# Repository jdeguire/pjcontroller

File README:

I need to put something here, I guess...

If you plan on building the firmware, you'll need a few things.
--avr-gcc (Ubuntu's repo has this as 'gcc-avr' for some reason)
--avr-binutils
--avr-libc
--avrdude
--scons, which in turn requires Python

The SConscript/SConstruct files assume that you are using the avr-gcc toolchain and avrdude as your ICSP programmer.  You can modify the files if this is not the case.

Schematics are created with KiCAD.

Stuff in hardware/spice was made using LTSpiceIV.  This runs fine under WINE.

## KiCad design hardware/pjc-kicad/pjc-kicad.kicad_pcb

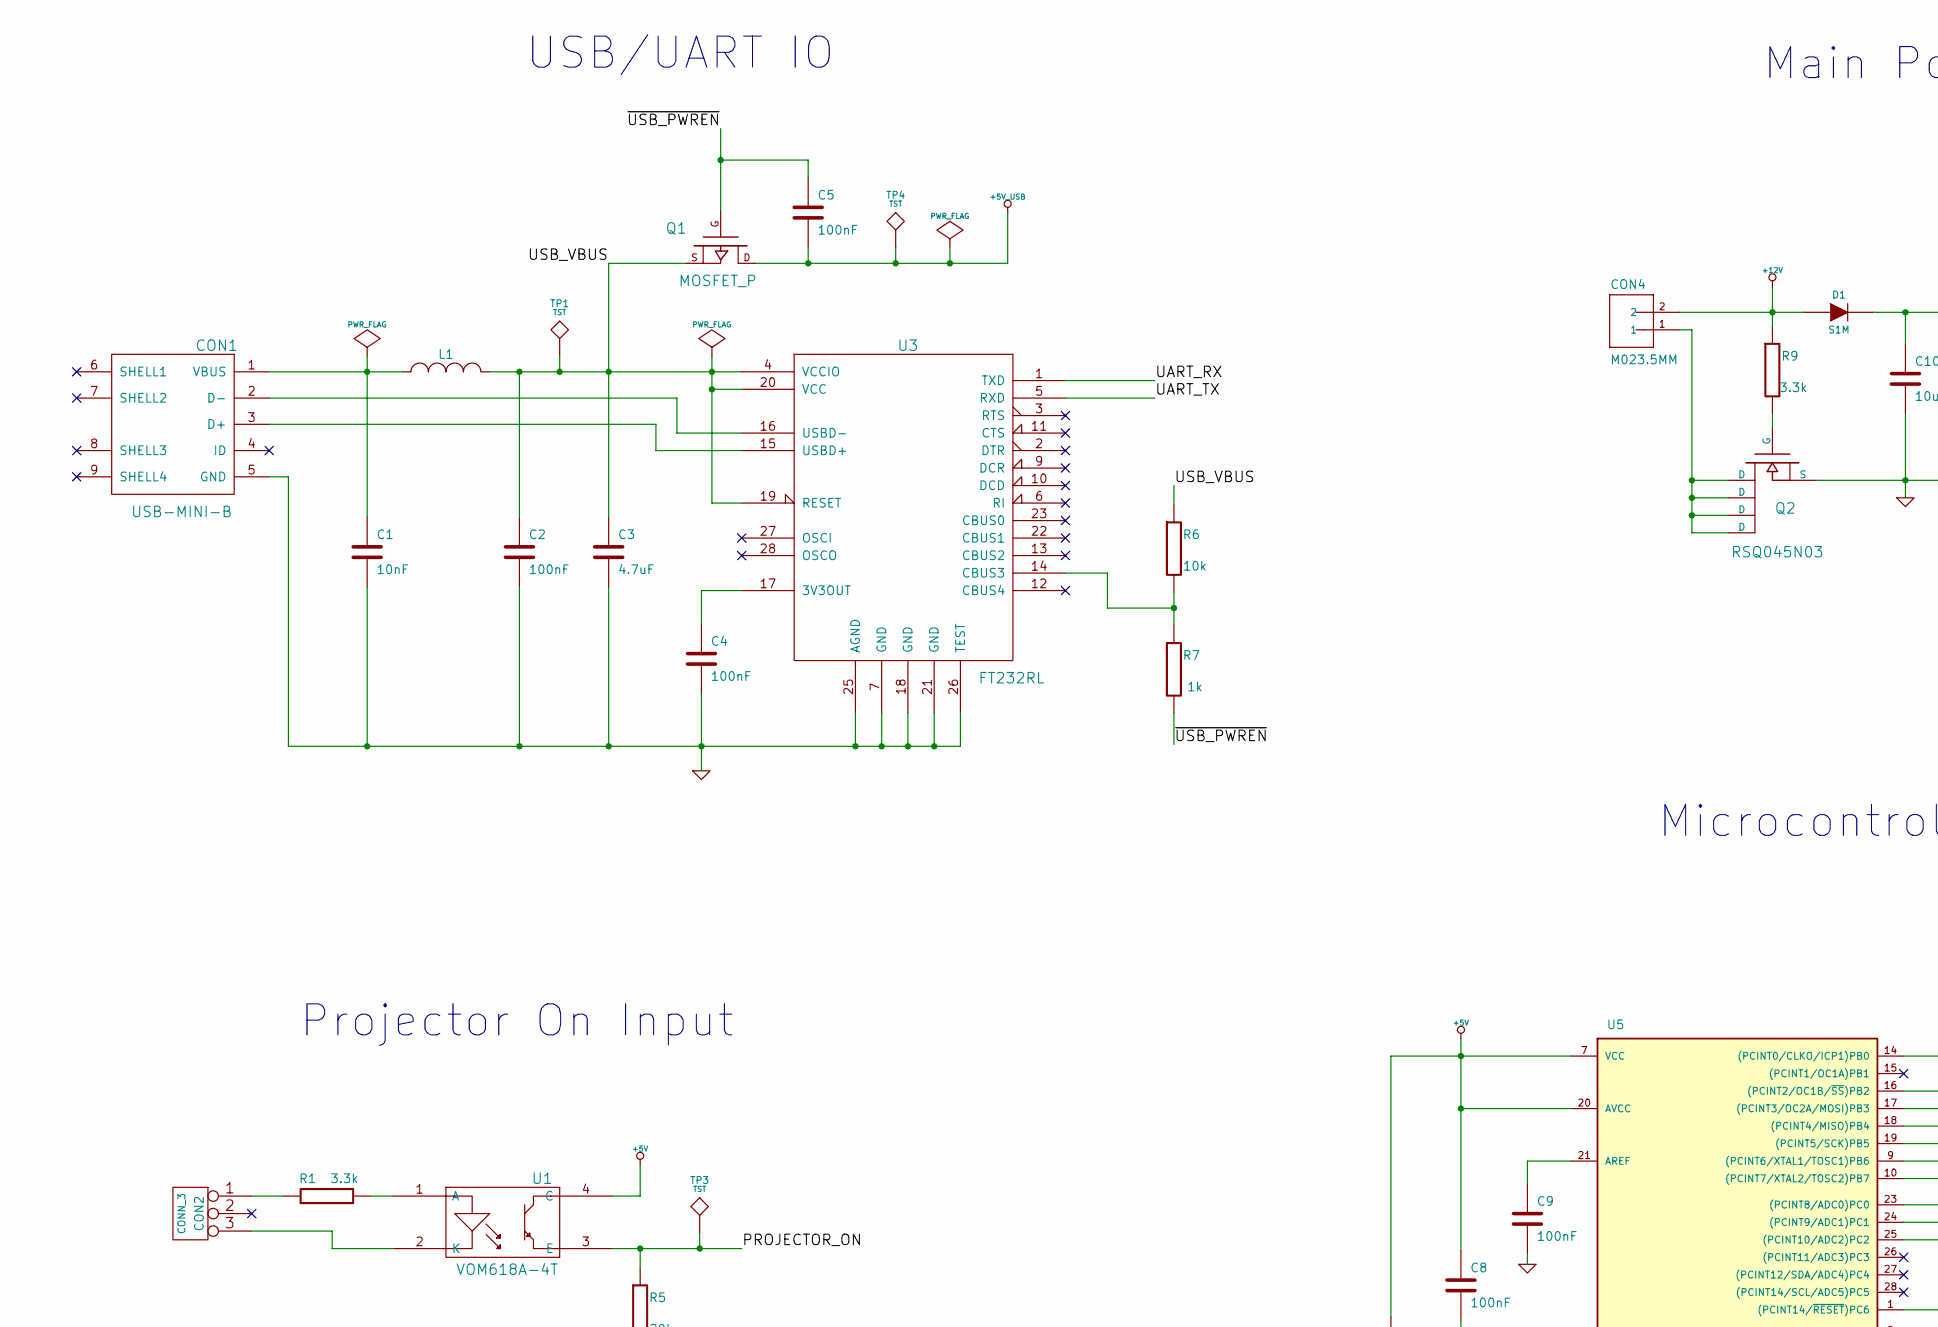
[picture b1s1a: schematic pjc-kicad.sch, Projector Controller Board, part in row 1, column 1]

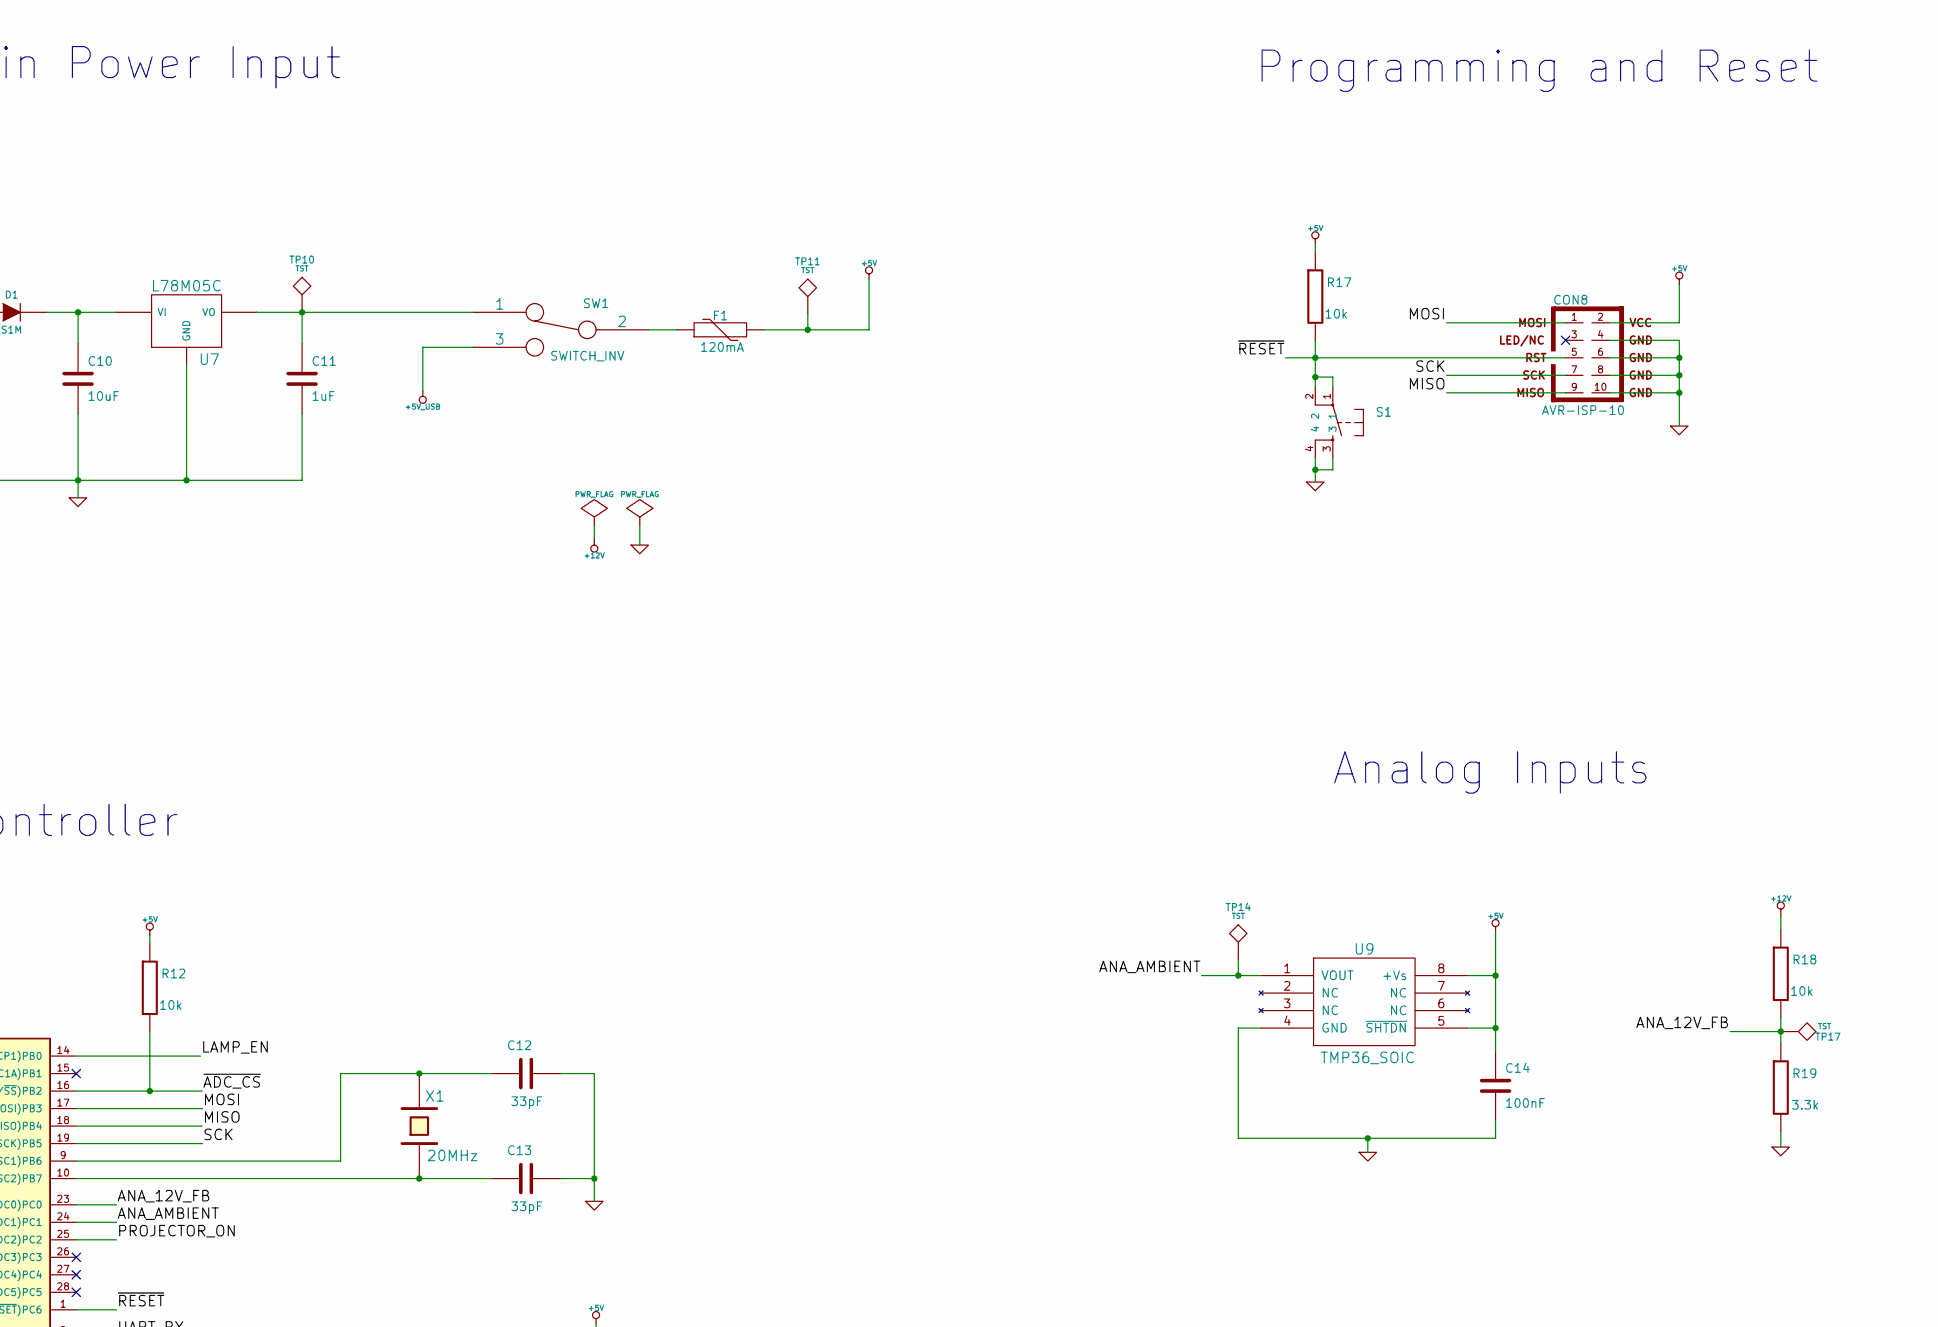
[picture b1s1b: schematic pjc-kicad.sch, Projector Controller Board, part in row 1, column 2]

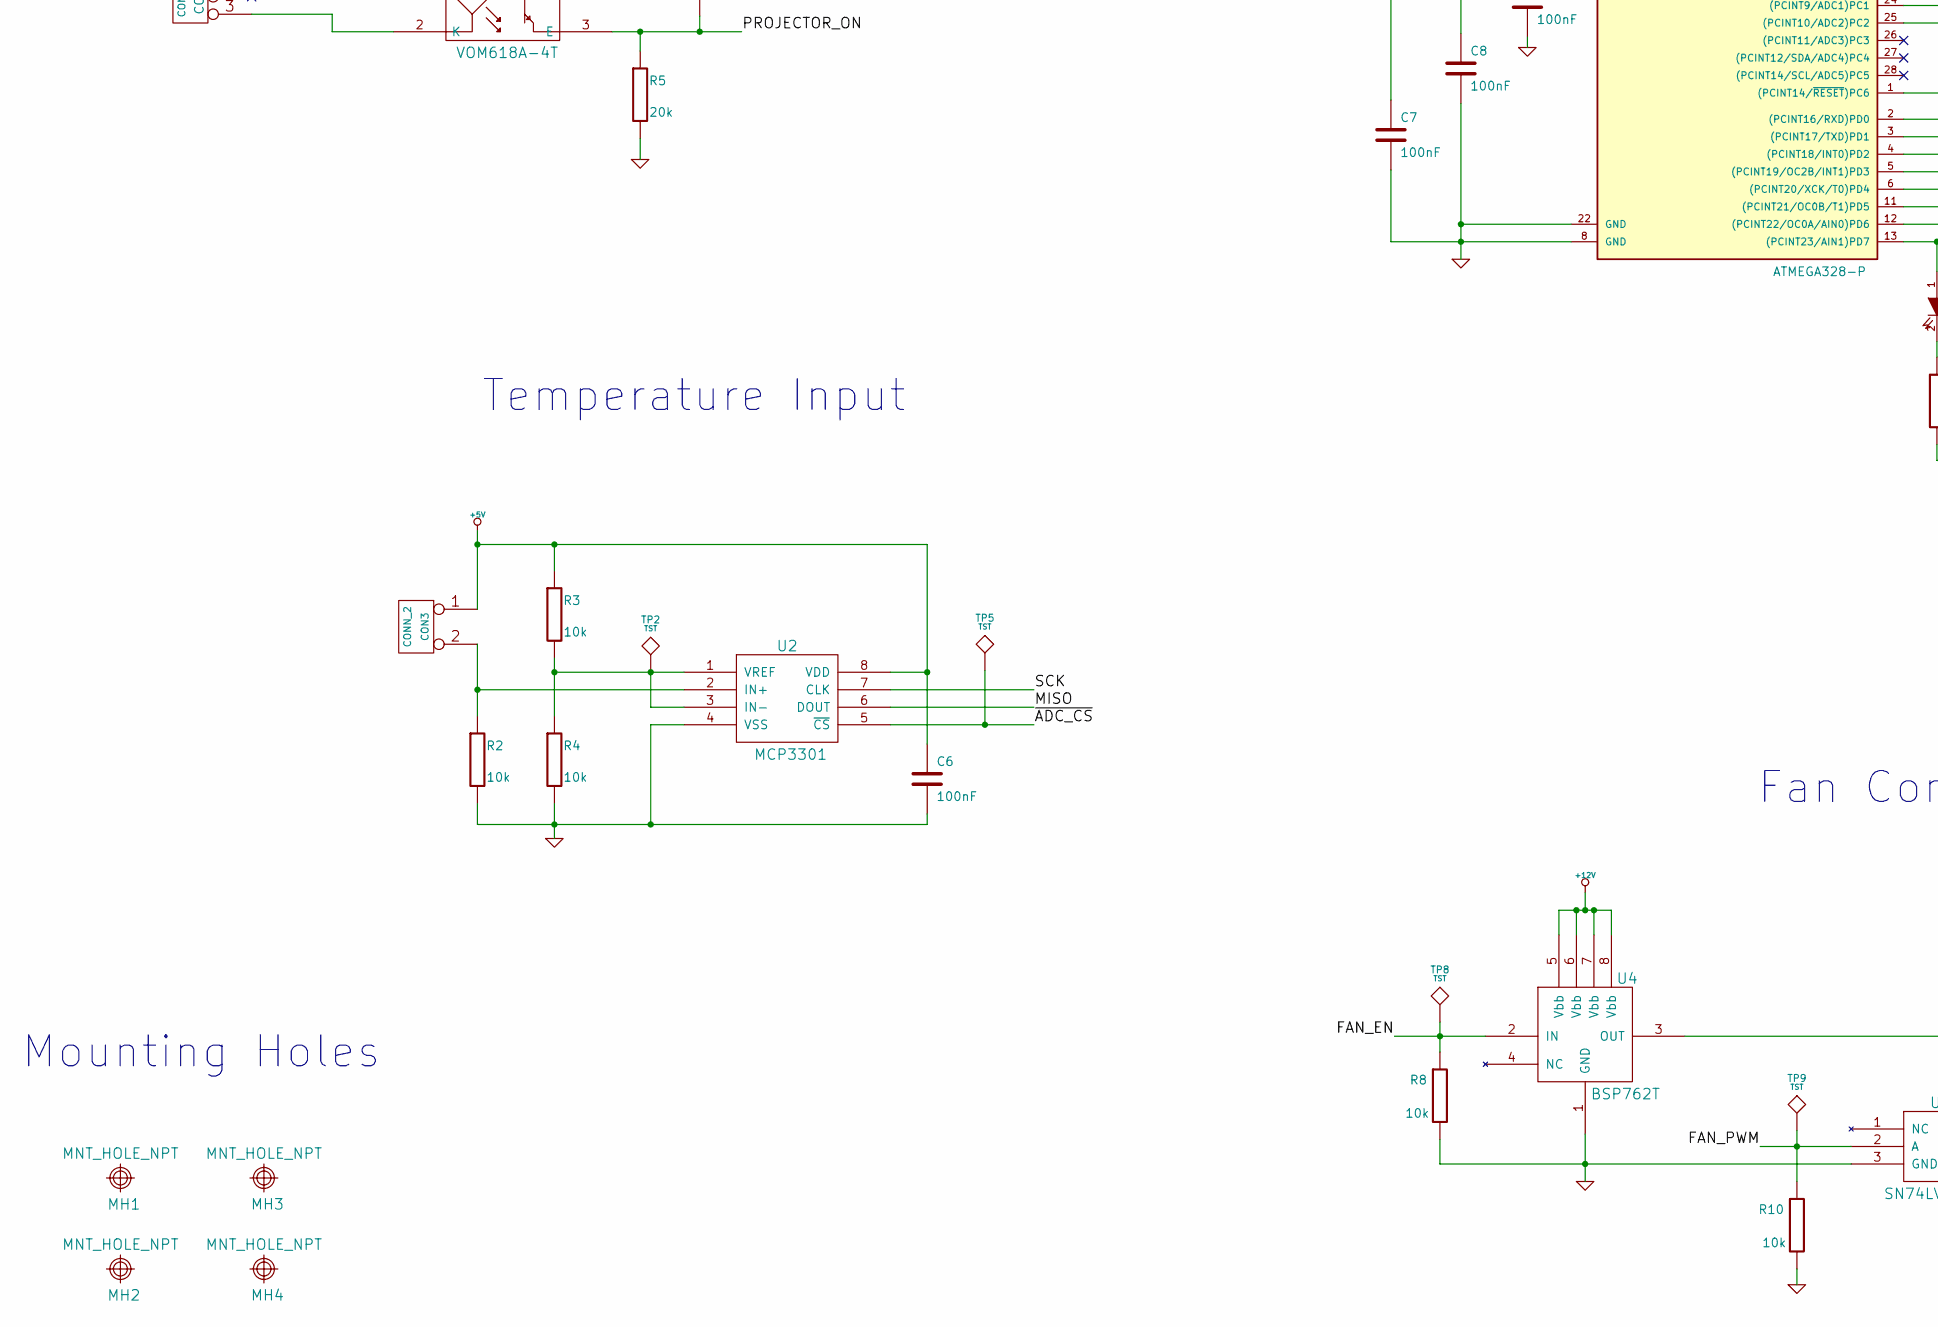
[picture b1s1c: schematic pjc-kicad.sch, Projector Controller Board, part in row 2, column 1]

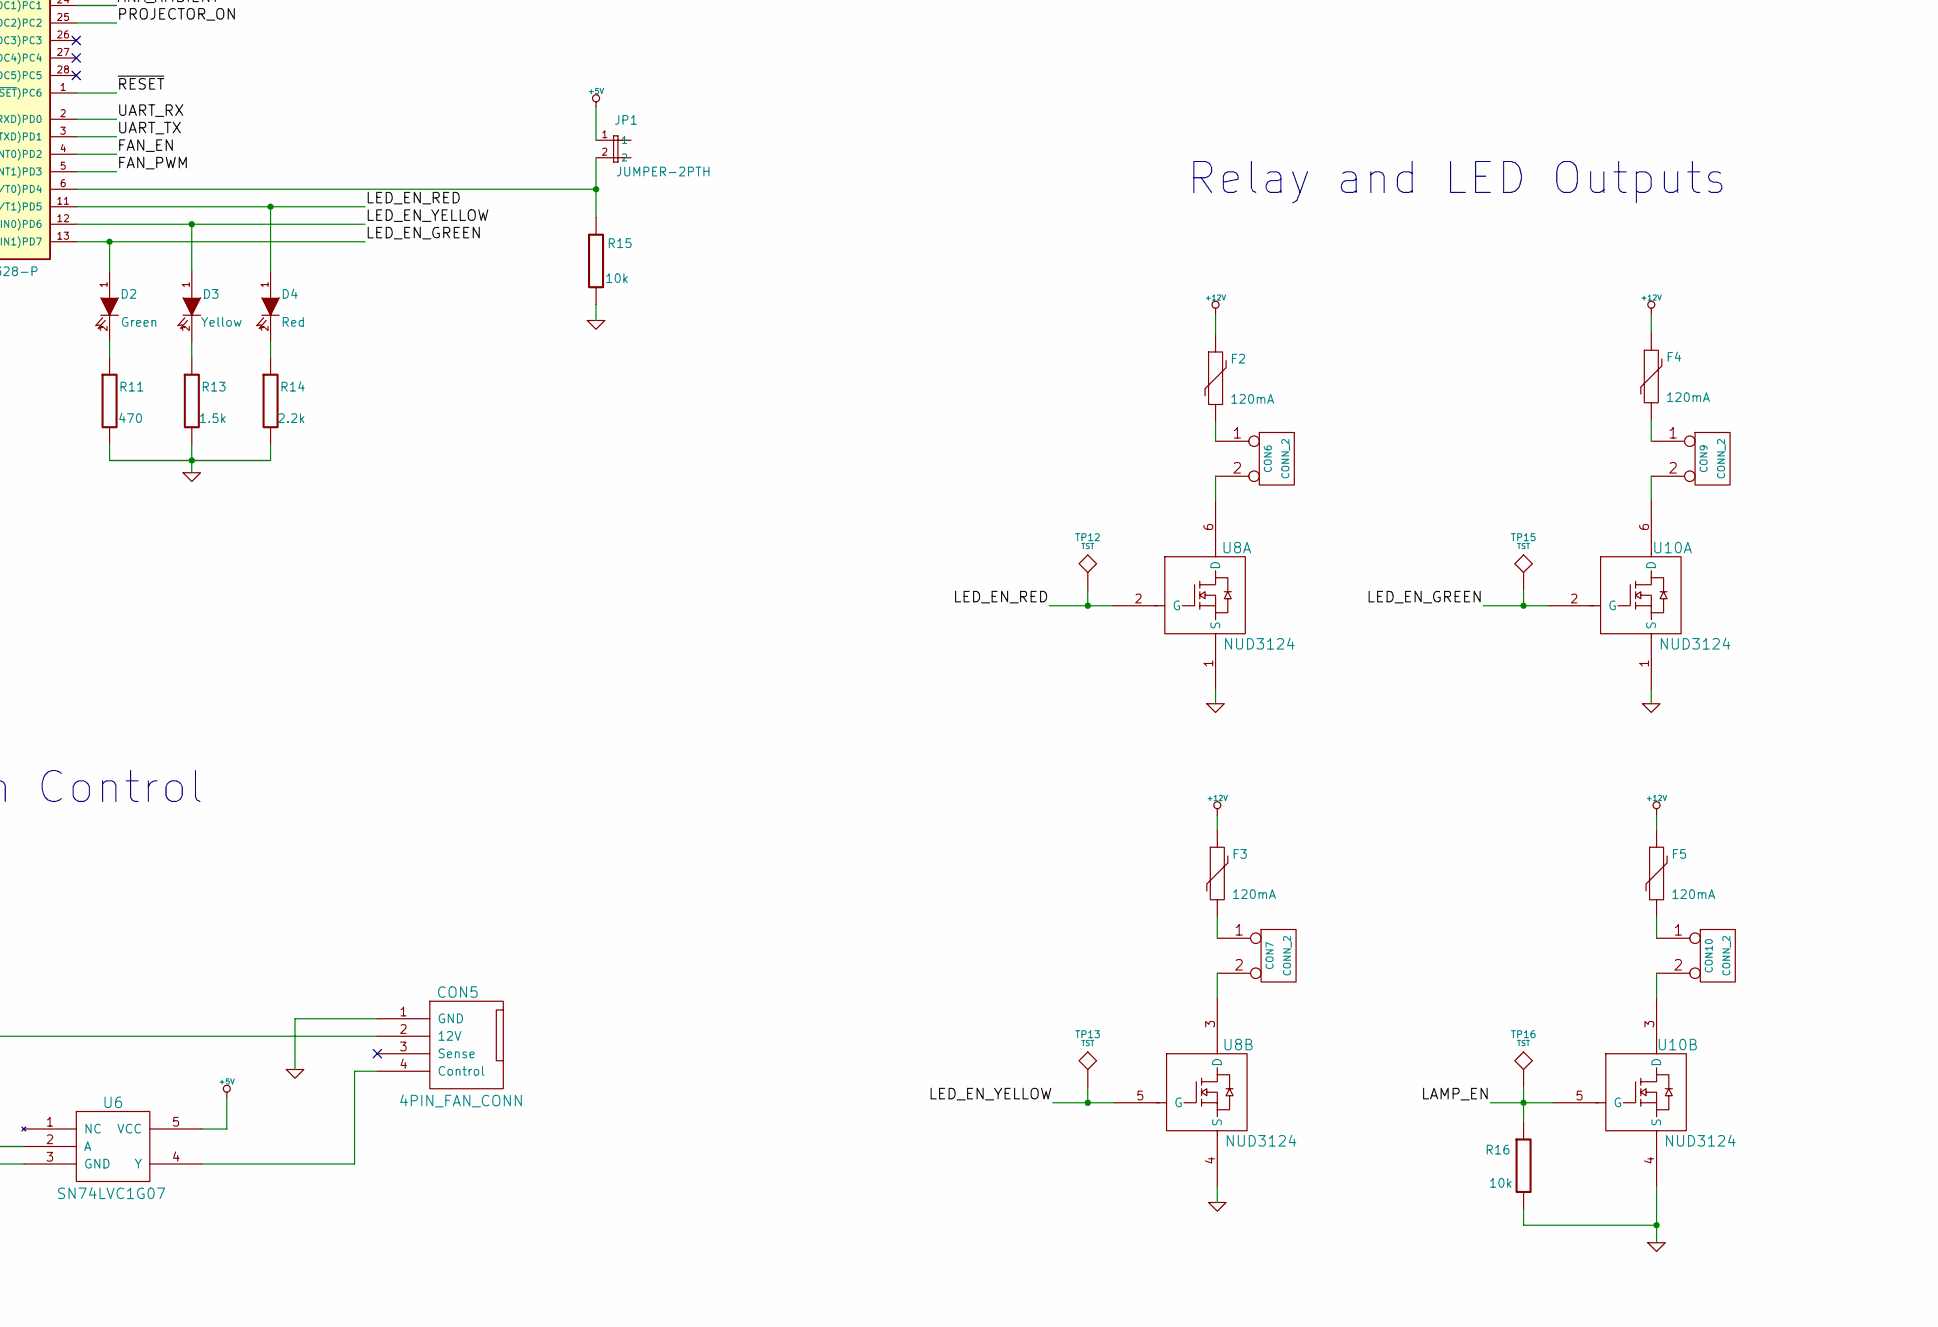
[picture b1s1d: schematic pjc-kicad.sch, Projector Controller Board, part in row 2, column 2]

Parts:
C1: 10nF
C2, C4, C5, C6, C7, C8, C9, C14: 100nF
C3: 4.7uF
C10: 10uF
C11: 1uF
C12, C13: 33pF
CON1: USB-MINI-B
CON2: CONN_3
CON3, CON6, CON7, CON9, CON10: CONN_2
CON4: M023.5MM; SparkFun-SCREWTERMINAL-3.5MM-2
CON5: 4PIN_FAN_CONN; 4PIN_FAN_PTH
CON8: AVR-ISP-10
D1: S1M
D2: Green
D3: Yellow
D4: Red
F1, F2, F3, F4, F5: 120mA
JP1: JUMPER-2PTH; SparkFun-1X02
L1: INDUCTOR_SMALL
MH1, MH2, MH3, MH4: MNT_HOLE_NPT
Q1: MOSFET_P
Q2: RSQ045N03
R1, R9, R19: 3.3k
R2, R3, R4, R6, R8, R10, R12, R15, R16, R17, R18: 10k
R5: 20k
R7: 1k
R11: 470
R13: 1.5k
R14: 2.2k
S1: TAC_SWITCHSMD; SparkFun-TACTILE_SWITCH_SMD
SW1: SWITCH_INV
TP1, TP2, TP3, TP4, TP5, TP8, TP9, TP10, TP11, TP12, TP13, TP14, TP15, TP16, TP17: TST
U1: VOM618A-4T
U2: MCP3301
U3: FT232RL
U4: BSP762T
U5: ATMEGA328-P; DIL28
U6: SN74LVC1G07; SOT23-5
U7: L78M05C
U8, U10: NUD3124
U9: TMP36_SOIC; SO8E
X1: 20MHz

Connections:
+5V: C6.1, C7.1, C8.1, C14.1, CON3.1, CON8.2, F1.2, JP1.1, R3.1, R12.1, R17.1, TP11.1, U1.4 (C), U2.8 (VDD), U5.7 (VCC), U5.20 (AVCC), U6.5 (VCC), U9.5 (~SHTDN), U9.8 (+Vs)
+5V_USB: C5.2, Q1.D, SW1.3, TP4.1
+12V: CON4.2, D1.1 (A), F2.1, F3.1, F4.1, F5.1, R9.1, R18.1, U4.5 (Vbb), U4.6 (Vbb), U4.7 (Vbb), U4.8 (Vbb)
/ANA_12V_FB: R18.2, R19.1, TP17.1, U5.23 ((PCINT8/ADC0)PC0)
/ANA_AMBIENT: TP14.1, U5.24 ((PCINT9/ADC1)PC1), U9.1 (VOUT)
/FAN_EN: R8.1, TP8.1, U4.2 (IN), U5.4 ((PCINT18/INT0)PD2)
/FAN_PWM: R10.1, TP9.1, U5.5 ((PCINT19/OC2B/INT1)PD3), U6.2 (A)
/LAMP_EN: R16.1, TP16.1, U5.14 ((PCINT0/CLKO/ICP1)PB0), U10.5 (G)
/LED_EN_GREEN: D2.1 (A), TP15.1, U5.13 ((PCINT23/AIN1)PD7), U10.2 (G)
/LED_EN_RED: D4.1 (A), TP12.1, U5.11 ((PCINT21/OC0B/T1)PD5), U8.2 (G)
/LED_EN_YELLOW: D3.1 (A), TP13.1, U5.12 ((PCINT22/OC0A/AIN0)PD6), U8.5 (G)
/MISO: CON8.9, U2.6 (DOUT), U5.18 ((PCINT4/MISO)PB4)
/MOSI: CON8.1, U5.17 ((PCINT3/OC2A/MOSI)PB3)
/PROJECTOR_ON: R5.1, TP3.1, U1.3 (E), U5.25 ((PCINT10/ADC2)PC2)
/SCK: CON8.7, U2.7 (CLK), U5.19 ((PCINT5/SCK)PB5)
/UART_RX: U3.1 (TXD), U5.2 ((PCINT16/RXD)PD0)
/UART_TX: U3.5 (RXD), U5.3 ((PCINT17/TXD)PD1)
/USB_VBUS: C2.1, C3.1, L1.2, Q1.S, R6.1, TP1.1, U3.4 (VCCIO), U3.19 (RESET), U3.20 (VCC)
/~ADC_CS: R12.2, TP5.1, U2.5 (~CS), U5.16 ((PCINT2/OC1B/~SS~)PB2)
/~RESET: CON8.5, R17.2, S1.1, S1.2, U5.1 ((PCINT14/~RESET~)PC6)
/~USB_PWREN: C5.1, Q1.G, R7.2
GND: C1.2, C2.2, C3.2, C4.2, C6.2, C7.2, C8.2, C9.2, C10.2, C11.2, C12.2, C13.2, C14.2, CON1.5 (GND), CON5.1 (GND), CON8.4, CON8.6, CON8.8, CON8.10, Q2.4 (S), R2.2, R4.2, R5.2, R8.2, R10.2, R11.2, R13.2, R14.2, R15.2, R16.2, R19.2, S1.3, S1.4, U2.4 (VSS), U3.7 (GND), U3.18 (GND), U3.21 (GND), U3.25 (AGND), U3.26 (TEST), U4.1 (GND), U5.8 (GND), U5.22 (GND), U6.3 (GND), U7.GND, U8.1 (S), U8.4 (S), U9.4 (GND), U10.1 (S), U10.4 (S)
unnamed: D4.2 (K), R14.1
unnamed: C4.1, U3.17 (3V3OUT)
unnamed: D2.2 (K), R11.1
unnamed: D3.2 (K), R13.1
unnamed: R3.2, R4.1, TP2.1, U2.1 (VREF), U2.3 (IN-)
unnamed: CON3.2 (PM), R2.1, U2.2 (IN+)
unnamed: C9.1, U5.21 (AREF)
unnamed: C10.1, D1.2 (K), U7.VI
unnamed: CON1.2 (D-), U3.16 (USBD-)
unnamed: CON1.3 (D+), U3.15 (USBD+)
unnamed: JP1.2, R15.1, U5.6 ((PCINT20/XCK/T0)PD4)
unnamed: R6.2, R7.1, U3.14 (CBUS3)
unnamed: C1.1, CON1.1 (VBUS), L1.1
unnamed: Q2.3 (G), R9.2
unnamed: CON5.2 (12V), U4.3 (OUT)
unnamed: CON5.4 (Control), U6.4 (Y)
unnamed: CON2.1, R1.1
unnamed: R1.2, U1.1 (A)
unnamed: CON2.3, U1.2 (K)
unnamed: C11.1, SW1.1, TP10.1, U7.VO
unnamed: CON6.2 (PM), U8.6 (D)
unnamed: CON9.2 (PM), U10.6 (D)
unnamed: CON7.2 (PM), U8.3 (D)
unnamed: CON10.2 (PM), U10.3 (D)
unnamed: CON9.1, F4.2
unnamed: CON4.1, Q2.1 (D), Q2.2 (D), Q2.5 (D), Q2.6 (D)
unnamed: CON6.1, F2.2
unnamed: CON10.1, F5.2
unnamed: CON7.1, F3.2
unnamed: F1.1, SW1.2
unnamed: C13.1, U5.10 ((PCINT7/XTAL2/TOSC2)PB7), X1.1
unnamed: C12.1, U5.9 ((PCINT6/XTAL1/TOSC1)PB6), X1.2

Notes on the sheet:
USB/UART IO
Main Power Input
Programming and Reset
Microcontroller
Projector On Input
Analog Inputs
Relay and LED Outputs
Fan Control
Temperature Input
Mounting Holes

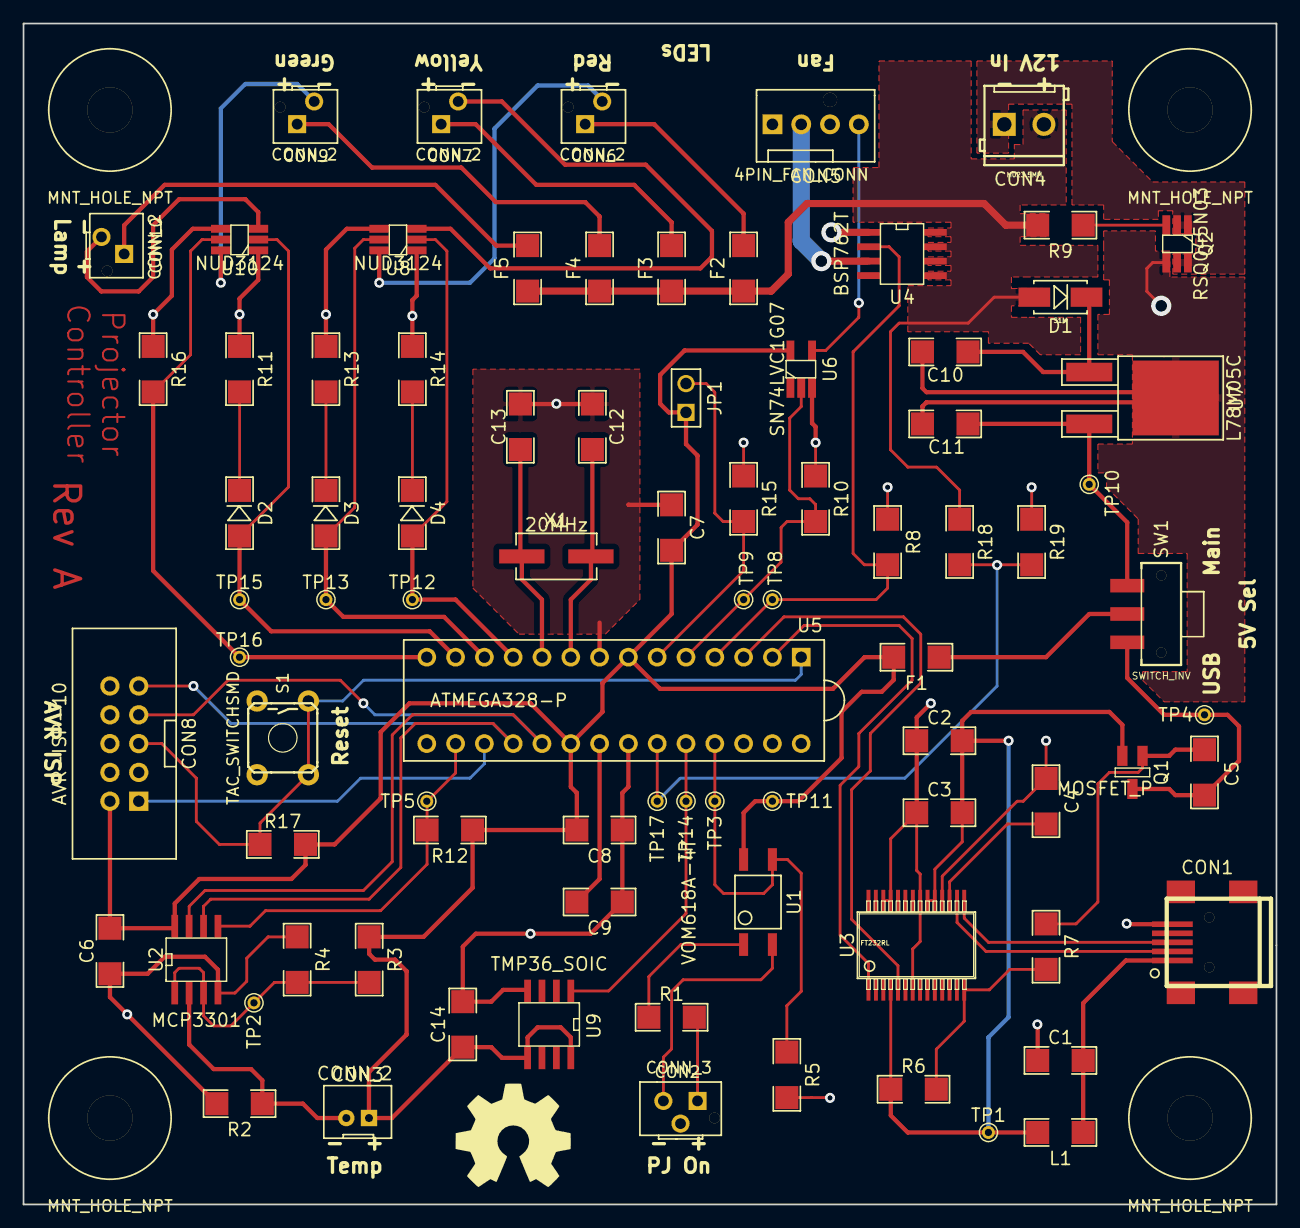
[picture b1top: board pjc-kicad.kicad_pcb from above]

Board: 2 copper layers, 110.5 x 104.1 mm, 88 parts (0 on the bottom side), 54 nets.

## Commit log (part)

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2010-11-05 Trying to create a repo.
    Oh yeah, it's on now.
2010-11-05 Adding a few more things...
2010-11-06 Fixed permissions issues. Now maybe stuff will commit.
2010-11-11 New custom linker script for the bootloader based off the avr5.x script included with avr-libc.
    This new linker script puts the code in the ATmega328's 4KB bootloader section at the high-end of flash and sets the correct sizes for the RAM and EEPROM spaces. We'll soon define SFR addresses in th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
2010-11-13 Added a new register map for making SFR access more convenient.
2010-11-16 New UART module.
    Current just has macros to convert a desired baud rate into a value for the baud
    rate register and for computing the baud rate error. This also throws an error if
    the baud rate generated by the baud rate register is off from the desired baud rate
    by more than 2%.
2010-11-29 New modules for programming the ATmega's flash memory.
2010-12-04 Added program memory functions to UART code and working on memlayout module for stuff shared between the bootloader and app.
2010-12-05 The device will no longer start up in the bootloader when first powered on.
    If the device was reset by the watchdog, we check a flag that says whether or not we
    should restart the app or stay in the bootloader. If it was reset by a different source,
    such as the external reset or power-on reset, then we'll load the app since that's the
    expected behavior.
2010-12-10 Basic command interface done; just need to actually add commands.
    Backspace now works as one would expect and the Escape key is used
    to clear the command buffer and reshow the prompt, effectively
    cancelling the command.
2010-12-18 CRC code now works
2011-01-31 Numerous improvments to bootloader.
    Removed the appinfo_t structure that was going to store the app
    CRC and number of pages within application space. Instead, I no
    longer care about the number of pages and the app's CRC will be
    stored in bootloader space. This simplifies code quite a bit as I
    was able to remove quite a bit of stuff from sharedmem.c.h and
    deviceprog.c.h, as well as the linker script.
2011-02-04 main() is ready to go.
    Got rid of testing stuff and broke out startup items into functions.
    Still need to shrink down the bootloader size.
    Changed lockbits in SConscript so that we can write to the bootloader
    section. Still debating whether to keep CRC at end of boot space or
    application space.
2011-02-06 Bootloader now feature-complete.
    Using just the -0s optimization, the bootloader comes out to about
    3975 bytes total.
    Added function to send a byte as hex digits out the serial port and
    another to convert an incoming hex string to a value. These are much
    smaller than using utoa and strtoul, which were the alternatives.
2011-02-10 Added compiler and linker optimization options.
    Reduced bootloader size by about 260 bytes.
2011-02-28 Fixed SConstruct and SConscript so that common modules are not built in the 'common/' directory.
2011-03-17 Added ability to read back serial responses from the bootloader.
2011-03-20 Implemented all of the PJC Bootloader's commands. Still need to test programming the bootloader, but everything else seems to work fine.
    Some methods require that the page size and number of pages in app space are entered into the
    PJCBootloader object's 'maxpages' and 'pagesize' fields. The methods getMaxPages() and
    getPageSize() ask the bootloader for this info and fill in those fields. The user could also just set those manually.
2011-03-23 Fixed EraseApp and EraseEEPROM commands.
2011-03-23 Change EraseEEPROM() to use eeprom_update_byte instead of eeprom_write_byte since the former can be much faster than the latter if much of EEPROM has nothing in it.
2011-05-12 Work on getting basic app build script going.
    Also removed the #!/bin/python line from the top of the build scripts so that they aren't runnable as stand-alone apps.
2011-05-13 Building a very basic app.
2011-05-14 Testing username issues...
2011-08-20 Dusting off the repo with some PySide.
    Adding a main.py so I can keep track of what I'm doing with PySide while I'm learning it.
2011-10-12 Some work on UI thread/Serial thread communication.
    Oh, there are threads now. A Dispatcher object was created to handle communication between threads and it seems to work okay so far. Now comes the task of making it work with the firmware.
2012-05-28 New Python class for storing a binary image of the contents of the AVR's flash memory. This pulls out functionality that was in the PJCBootloader class, but that really shouldn't have been.
2012-05-28 Minor update to the connectors I want to use.
    I also put some LED info in there only because that'll come in handly later on.
2012-05-29 Updates to get the firmware upgrade working again after making the changes from the previous commit.
2012-05-30 Newest version of PWM fan spec.
    This one seems to have more info about what the fan controller should be doing, which ought to be helpful.
2012-06-03 Forgot to put these in the last commit.
    Adding a new file for the communication thread and removing the dispatcher since it is no longer needed (now using Qt signals and slots).
2012-06-17 Moved serial combo box and buttons into MainWindow.
2012-07-08 Multiple changes to bootloader code, including change in how updates are performed.
    Renamed system.h to appcfg.h since that seems more appropriate for what the file does (did this for app as well).
    Made filling the AVR's flash write latches a separate function from programming a page.
    Erasing EEPROM now manually uses the AVR erase-only mode and erases only cells that are not already clear. This no longer uses the AVR libc function for writing to EEPROM since that always uses erase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
    Loading page data is now a separate serial command from programming the page. This makes programming easier since one no longer has a small window in which to write binary data over the serial por
2012-07-09 Clear watchdog after every flash page erase.
2012-07-10 Add commands to the app and fix an issue in common code.
    Clear watchdog when grabbing new command data in Cmd_ProcessInterface. Weird errors were popping up while testing the software and this seemed to be the issue.
    Add a few basic serial commands to the application and have it run the command interface. This now allows the app to work with the software, which assumes that the app can jump to the bootloader and 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
2012-07-15 Added new signal/slot manager class and fixed the worker thread.
    The new ConnectionManager class makes it easier to pair signals with slots by conecting signals and slots with the same given name automatically.
    It also turns out that you are not supposed to inherit from QThread but rather create your separate class and move it to a new QThread using the moveToThread() method. See http://labs.qt.nokia.com/20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
2012-08-16 Begun exception handling for slots in the SerialComm class.
2012-09-04 Added settings page to modify basic application settings such as minimum fan speed, overtemp limit, etc. Still needs testing.
2012-09-07 App is mostly complete, with all of the currently-planned pages and features available.
    Still needs testing and a bit more error handling. I may look into setting the app up for translations in the future. I still need to figure out how to use Py2Exe to get a Windows vesrion.
2012-09-09 Software now feature complete and handles various errors appropriately.
    The firmware now uses macros for their LED pins.
2012-09-12 Software app runs under Windows with Py2exe!
    File setup.py contains the Py2exe config and the output is put into the
    dist/ subdirectory. Also including the Visual C++ 2008 Redistributable
    runtime since the built app will need that to run.
    The software now has a real name in its window frame and prints a version
    number (just a date code) on startup.
    Added a couple of parts to the parts list. I think the major parts have
2013-01-06 Add new KiCAD project
2013-01-07 More work on schematic and moved some stuff around.
2013-01-14 Add more datasheets as schematic moves toward completion.
2013-01-15 Add zener part
2013-01-22 lots more datasheets as schematic moves very close to completion
2013-01-29 Add pull-downs where needed to outputs and fix test points
2013-02-02 Added GPLv3 header to source code files.
2013-02-06 Updated README, added CC BY-SA license text, added start of Developers Guide, and remove LTSPICE files since they're old and no longer useful.
2013-02-07 Completed a couple of circuit detail sections for the hardware.
2013-02-09 Completed circuit descriptions
2013-02-12 More work done on Firmware portion of dev guide
2013-02-15 More work on Firmware section of doc and put 20kOhm pulldown on opto collector to reduce the current needed to saturate it (useful for 3.3V inputs).
2013-02-16 Modify LED code to be easier to use with functional macros.
2013-02-17 Add setting to set lamp delay off time, which is how long the firmware will wait before actually turning off the lamp.
    Also remove the circle-C copyright symbol since Python whines about it.
2013-02-17 fix typo
2013-02-17 Completed Firmware section and started Software section
2013-02-22 Completed Dev Guide draft.
    Changed 20MHz oscillator to one with smaller package.
2013-02-22 Update Steinhart-Hart equation and add devguie PDF to repo.
2013-02-23 Modify wording for how to handle Microchip ADC reading of -4096, which indicates a missing thermistor.
2013-02-24 Add datasheet for new Rohm Semi part.
2013-02-24 Changed button part number from FSM4JH to 3-1977120-6 and updated datasheet.
    Tyco changed the part number and marked the old one as suspended, but no vendors seem to know that and still use the old part number (FSM4JH), which means that this is probably a very recent change.
2013-02-24 Fix schematic errors found by KiCad and create symbol<-->footprint associations
2013-02-25 Began laying out board
2013-03-01 Completed USB portion of layout
2013-03-02 Use 33pF caps on crystal instead of 22pF in order to more closely match the crystal's load capacitance
2013-03-04 Changed crystal oscillator caps to 33pF
2013-03-04 More layout work.
    Rearranged a couple of pieces to reduce space (still working on that) and wired up more areas, including the ISP connector.
2013-03-08 Board layout done!
    Need to change NPTH mechanical holes to PTH holes since KiCad generates a second drill file for NPTH holes, which won't work.
2013-03-09 Change from BatchPCB manufacture to OSH Park.
2013-03-09 Just sent board for manufacture!
    The modules in pjc.mod that were derived from the SparkFun library had the reference text on the wrong layer, so those had to be corrected by hand.
2013-03-09 Update README.txt to make it not totally worthless.
    Minor update to BoM.
